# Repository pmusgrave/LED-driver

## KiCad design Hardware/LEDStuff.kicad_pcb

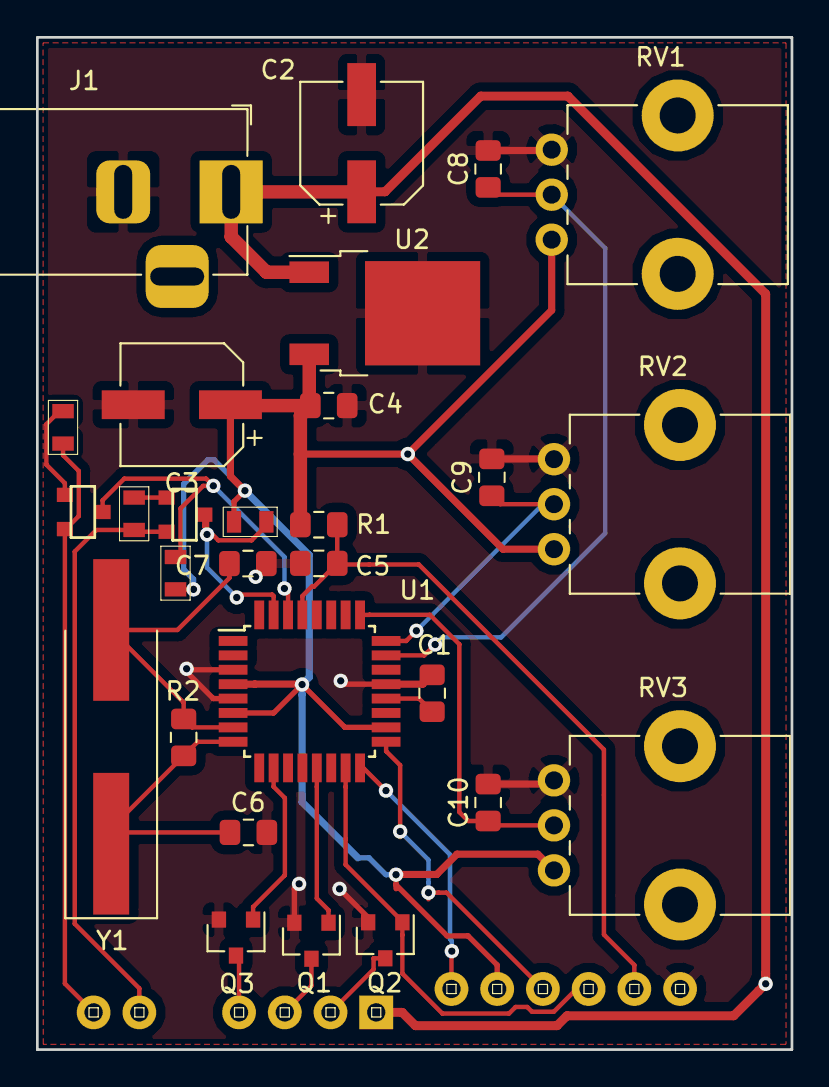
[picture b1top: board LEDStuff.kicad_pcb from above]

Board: 2 copper layers, 41.9 x 56.2 mm, 31 parts (0 on the bottom side), 24 nets.

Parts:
C1, C4, C5: 0.1uF; C_0805_2012Metric_Pad1.15x1.40mm_HandSolder
C2, C3: 47uF; CP_Elec_6.3x7.7
C6, C7: 22pF; C_0805_2012Metric_Pad1.15x1.40mm_HandSolder
C8, C9, C10: 1u; C_0805_2012Metric_Pad1.15x1.40mm_HandSolder
J1: Barrel_Jack; BarrelJack_Horizontal
J2: AVR-ISP-6; 1X06
J3: Conn_01x04_Male; 1X04
J4: UART; 1X02
Q1, Q2, Q3: Q_NMOS_GSD; SOT-23
Q4, Q5: MOSFET-NCHANNELBSS138; SOT23-3
R1: 4.7k; R_0805_2012Metric_Pad1.15x1.40mm_HandSolder
R2: 1M; R_0805_2012Metric_Pad1.15x1.40mm_HandSolder
R3, R4, R5, R6: R; 0805
RV1, RV2, RV3: 10k; Potentiometer_Bourns_PTV09A-1_Single_Vertical
U1: ATMEGA328P-AU; TQFP-32_7x7mm_P0.8mm
U2: LM7805_TO220; TO-252-2
Y1: 16MHz; Crystal_SMD_HC49-SD_HandSoldering

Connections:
+5V: C3.1, C4.1, J2.2, R1.1, R3.1, R4.1, RV1.1, RV2.1, RV3.1, U1.4, U1.6, U1.18, U2.3
+12V: C2.1, J1.1, J3.1, U2.1
/BLUE_LED_OUT: J3.4, Q3.3
/BLUE_POT: C10.1, RV3.2, U1.25
/BLUE_PWM_OUT: Q3.1, U1.10
/GREEN_LED_OUT: J3.2, Q2.3
/GREEN_POT: C9.1, RV2.2, U1.24
/GREEN_PWM_OUT: J2.4, Q2.1, U1.15
/MISO: J2.1, U1.16
/RED_LED_OUT: J3.3, Q1.3
/RED_POT: C8.1, RV1.2, U1.23
/RED_PWM_OUT: Q1.1, U1.13
/RESET: C5.1, J2.5, R1.2, U1.29
/RXD: Q4.3, R4.2, U1.30
/SCK: J2.3, U1.17
/UART_RX_LEVELSHIFTED: J4.1, Q4.2, R6.2
/UART_TX_LEVELSHIFTED: J4.2, Q5.2, R5.2
/XTAL1: C7.1, R2.1, U1.7, Y1.2
/XTAL2: C6.1, R2.2, U1.8, Y1.1
GND: C1.2, C2.2, C3.2, C4.2, C5.2, C6.2, C7.2, C8.2, C9.2, C10.2, J1.2, J2.6, Q1.2, Q2.2, Q3.2, RV1.3, RV2.3, RV3.3, U1.3, U1.5, U1.21, U2.2
unnamed: C1.1, U1.20
unnamed: Q4.1, R6.1
unnamed: Q5.1, R5.1
unnamed: Q5.3, R3.2, U1.31

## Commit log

2018-12-13 initial commit potentiometers control R,G, and B LED light levels
2018-12-13 add Kicad schematic and PCB files
2018-12-13 change directory structure
2018-12-13 rename program script to program.sh
2018-12-13 begin to read AM2302 temp sensor
2018-12-15 testing SPI master/slave comm
2018-12-19 SPI communication is working between RPi as master and atmega328p as slave, without any level shifting hardware. To prevent overvoltage damage to RPi, do not use any pullup resistors to 5V and leave 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
2018-12-19 SPI communication is working SPI master
2018-12-19 test driving PWM from an SPI signal
2018-12-19 prepare atmega328p to receive SPI commands master will send separate SPI packets in the form: R, G, or B, followed by the PWM value for that color. e.g. R 100 G 255 B 100
2018-12-19 change character constants to ASCII code
2018-12-19 testing SPI master code with ASCII
2018-12-19 test fading all LED colors via SPI
2018-12-19 slave code receives SPI messages and fades LEDs
2019-01-01 SPI comms fully functioning AVR can receive SPI signals and set R,G, and B values sent from a master device
2019-01-01 SPI master devices sends an incrementing value on all three channels clock rate slowed down as much as possible to avoid missed SPI messages
2019-01-01 add GPIO to signal start of SPI transmission from master device This is because the atmega328p-au shares MOSI with a timer OC pin which is needed for PWM. Disable SPI until the master starts sending 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
2019-01-01 add GPIO to master device
2019-01-01 change SPI Start pin for custom PCB
2019-01-01 remove debug code
2019-01-02 update build process
2019-01-02 clean up tests
2019-01-02 uart modules for debugging
2019-01-02 rename led and spi to more sensible filenames
2019-12-05 google home example code compiles but cannot add smart devices or connect to google home
2019-12-05 Revert "google home example code"
    This reverts commit 4ef00bc483f4924521567924cab2cbfcfec7f4b9.
    Starting a new branch for the google home stuff, so remove it from master branch.
2019-12-17 board v2 add UART pins, 3.3V to 5V level shifter, change headers to standard 0.1" pin pitch
2020-01-13 receive RGB values from host via UART serial
2020-01-13 RPI serial test program
